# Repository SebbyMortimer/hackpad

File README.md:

# Sebby's Hackpad

My personal hackpad for being a power user and probably do something funny. It has 4 buttons, 2 LEDs and an OLED panel.

This is my second time creating a PCB (my first was the "blinky" LED chaser) so I'm still heavily relying on the guide to get me a working macropad, but I was able to add an OLED panel to it with some help from the Hack Club Slack community. I have worked with CAD software a lot in school and we use Autodesk Inventor instead of Fusion 360 so that's why I used Inventor when creating the case, it was a pretty similar process though.

BOM:
- 1x Seeed XIAO RP2040
- 4x MX-Style switches
- 1x 0.91 inch OLED display
- 4x Blank DSA keycaps (White)
- 2x SK6812 MINI-E LEDs
- 4x M3x16mm screws
- 4x M3x5mx4mm heatset inserts

| Schematic | PCB | Case |
| --- | --- | --- |
||||

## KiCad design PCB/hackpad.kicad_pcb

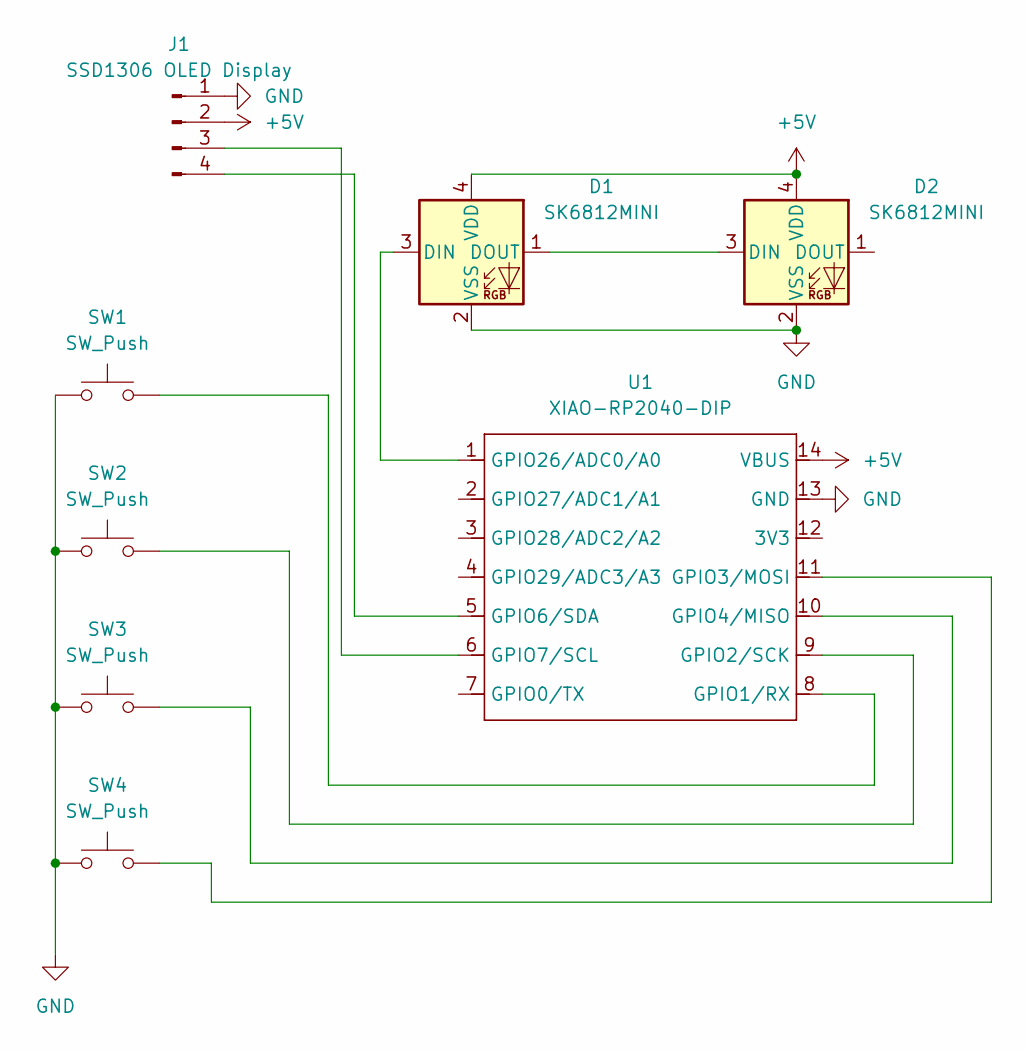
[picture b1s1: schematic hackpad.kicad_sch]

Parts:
D1, D2: SK6812MINI; LED_SK6812MINI_PLCC4_3.5x3.5mm_P1.75mm
J1: SSD1306 OLED Display; SSD1306-0.91-OLED-4pin-128x32
SW1, SW2, SW3, SW4: SW_Push; SW_Cherry_MX_1.00u_PCB
U1: XIAO-RP2040-DIP

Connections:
+5V: D1.4 (VDD), D2.4 (VDD), J1.2, U1.14 (VBUS)
GND: D1.2 (VSS), D2.2 (VSS), J1.1, SW1.1, SW2.1, SW3.1, SW4.1, U1.13 (GND)
unnamed: D1.3 (DIN), U1.1 (GPIO26/ADC0/A0)
unnamed: D1.1 (DOUT), D2.3 (DIN)
unnamed: J1.3, U1.6 (GPIO7/SCL)
unnamed: J1.4, U1.5 (GPIO6/SDA)
unnamed: SW1.2, U1.8 (GPIO1/RX)
unnamed: SW2.2, U1.9 (GPIO2/SCK)
unnamed: SW4.2, U1.11 (GPIO3/MOSI)
unnamed: SW3.2, U1.10 (GPIO4/MISO)

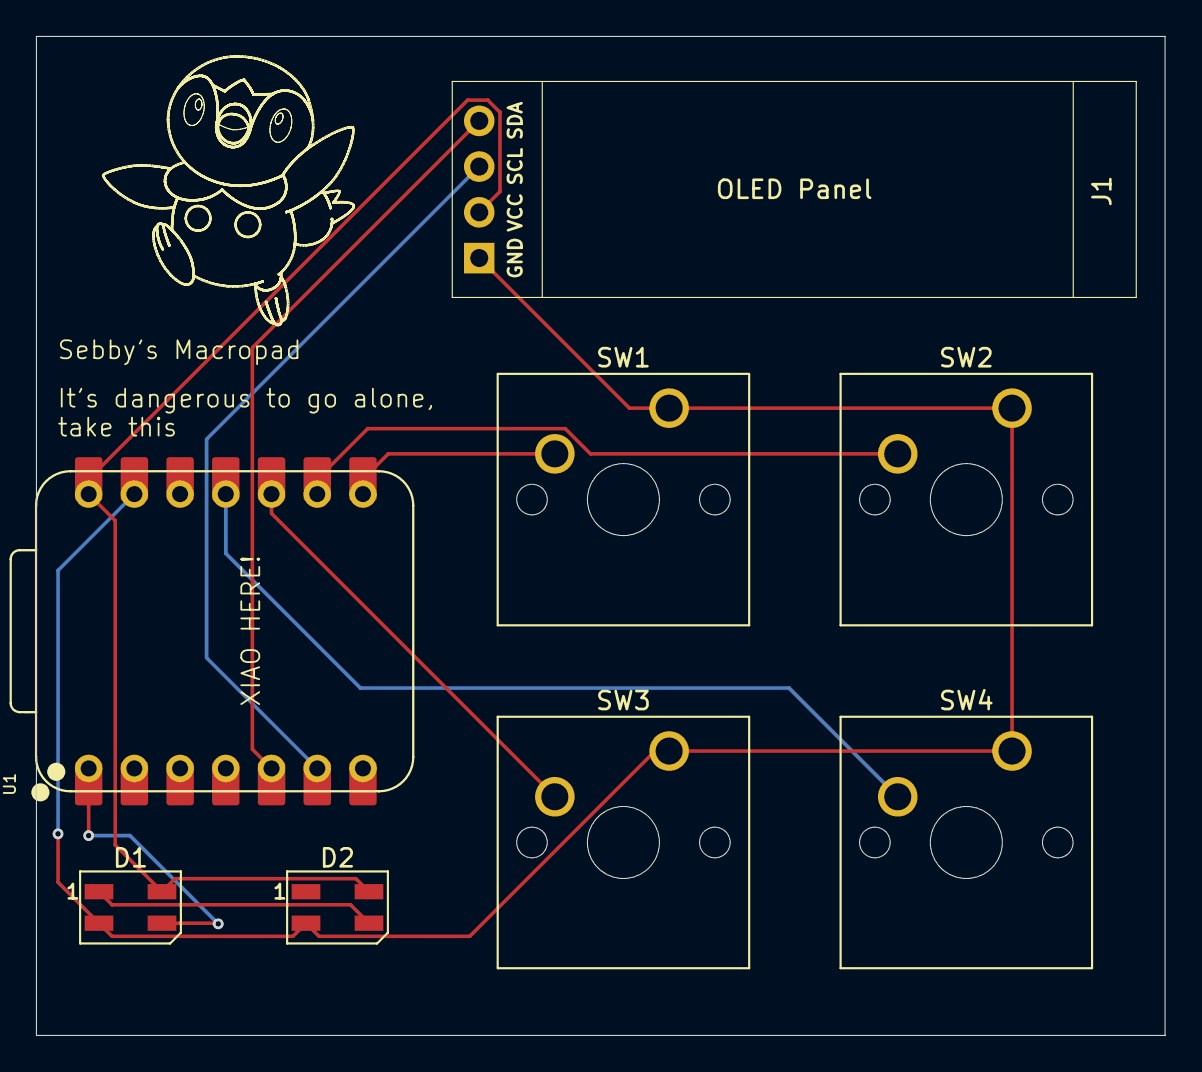
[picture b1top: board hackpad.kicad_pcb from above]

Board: 2 copper layers, 62.7 x 55.5 mm, 8 parts (0 on the bottom side), 10 nets.

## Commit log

2025-12-26 Add files
2025-12-26 Add image of PCB in case
